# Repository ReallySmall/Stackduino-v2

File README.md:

Stackduino 2
==========
Please visit the project site for details: https://www.stackduino.net/boards/v2-2

Copyright 2017 Richard Iles

Permission is hereby granted, free of charge, to any person obtaining a copy of this software and associated documentation files (the "Software"), to deal in the Software without restriction, including without limitation the rights to use, copy, modify, merge, publish, distribute, sublicense, and/or sell copies of the Software, and to permit persons to whom the Software is furnished to do so, subject to the following conditions:

The above copyright notice and this permission notice shall be included in all copies or substantial portions of the Software.

THE SOFTWARE IS PROVIDED "AS IS", WITHOUT WARRANTY OF ANY KIND, EXPRESS OR IMPLIED, INCLUDING BUT NOT LIMITED TO THE WARRANTIES OF MERCHANTABILITY, FITNESS FOR A PARTICULAR PURPOSE AND NONINFRINGEMENT. IN NO EVENT SHALL THE AUTHORS OR COPYRIGHT HOLDERS BE LIABLE FOR ANY CLAIM, DAMAGES OR OTHER LIABILITY, WHETHER IN AN ACTION OF CONTRACT, TORT OR OTHERWISE, ARISING FROM, OUT OF OR IN CONNECTION WITH THE SOFTWARE OR THE USE OR OTHER DEALINGS IN THE SOFTWARE.

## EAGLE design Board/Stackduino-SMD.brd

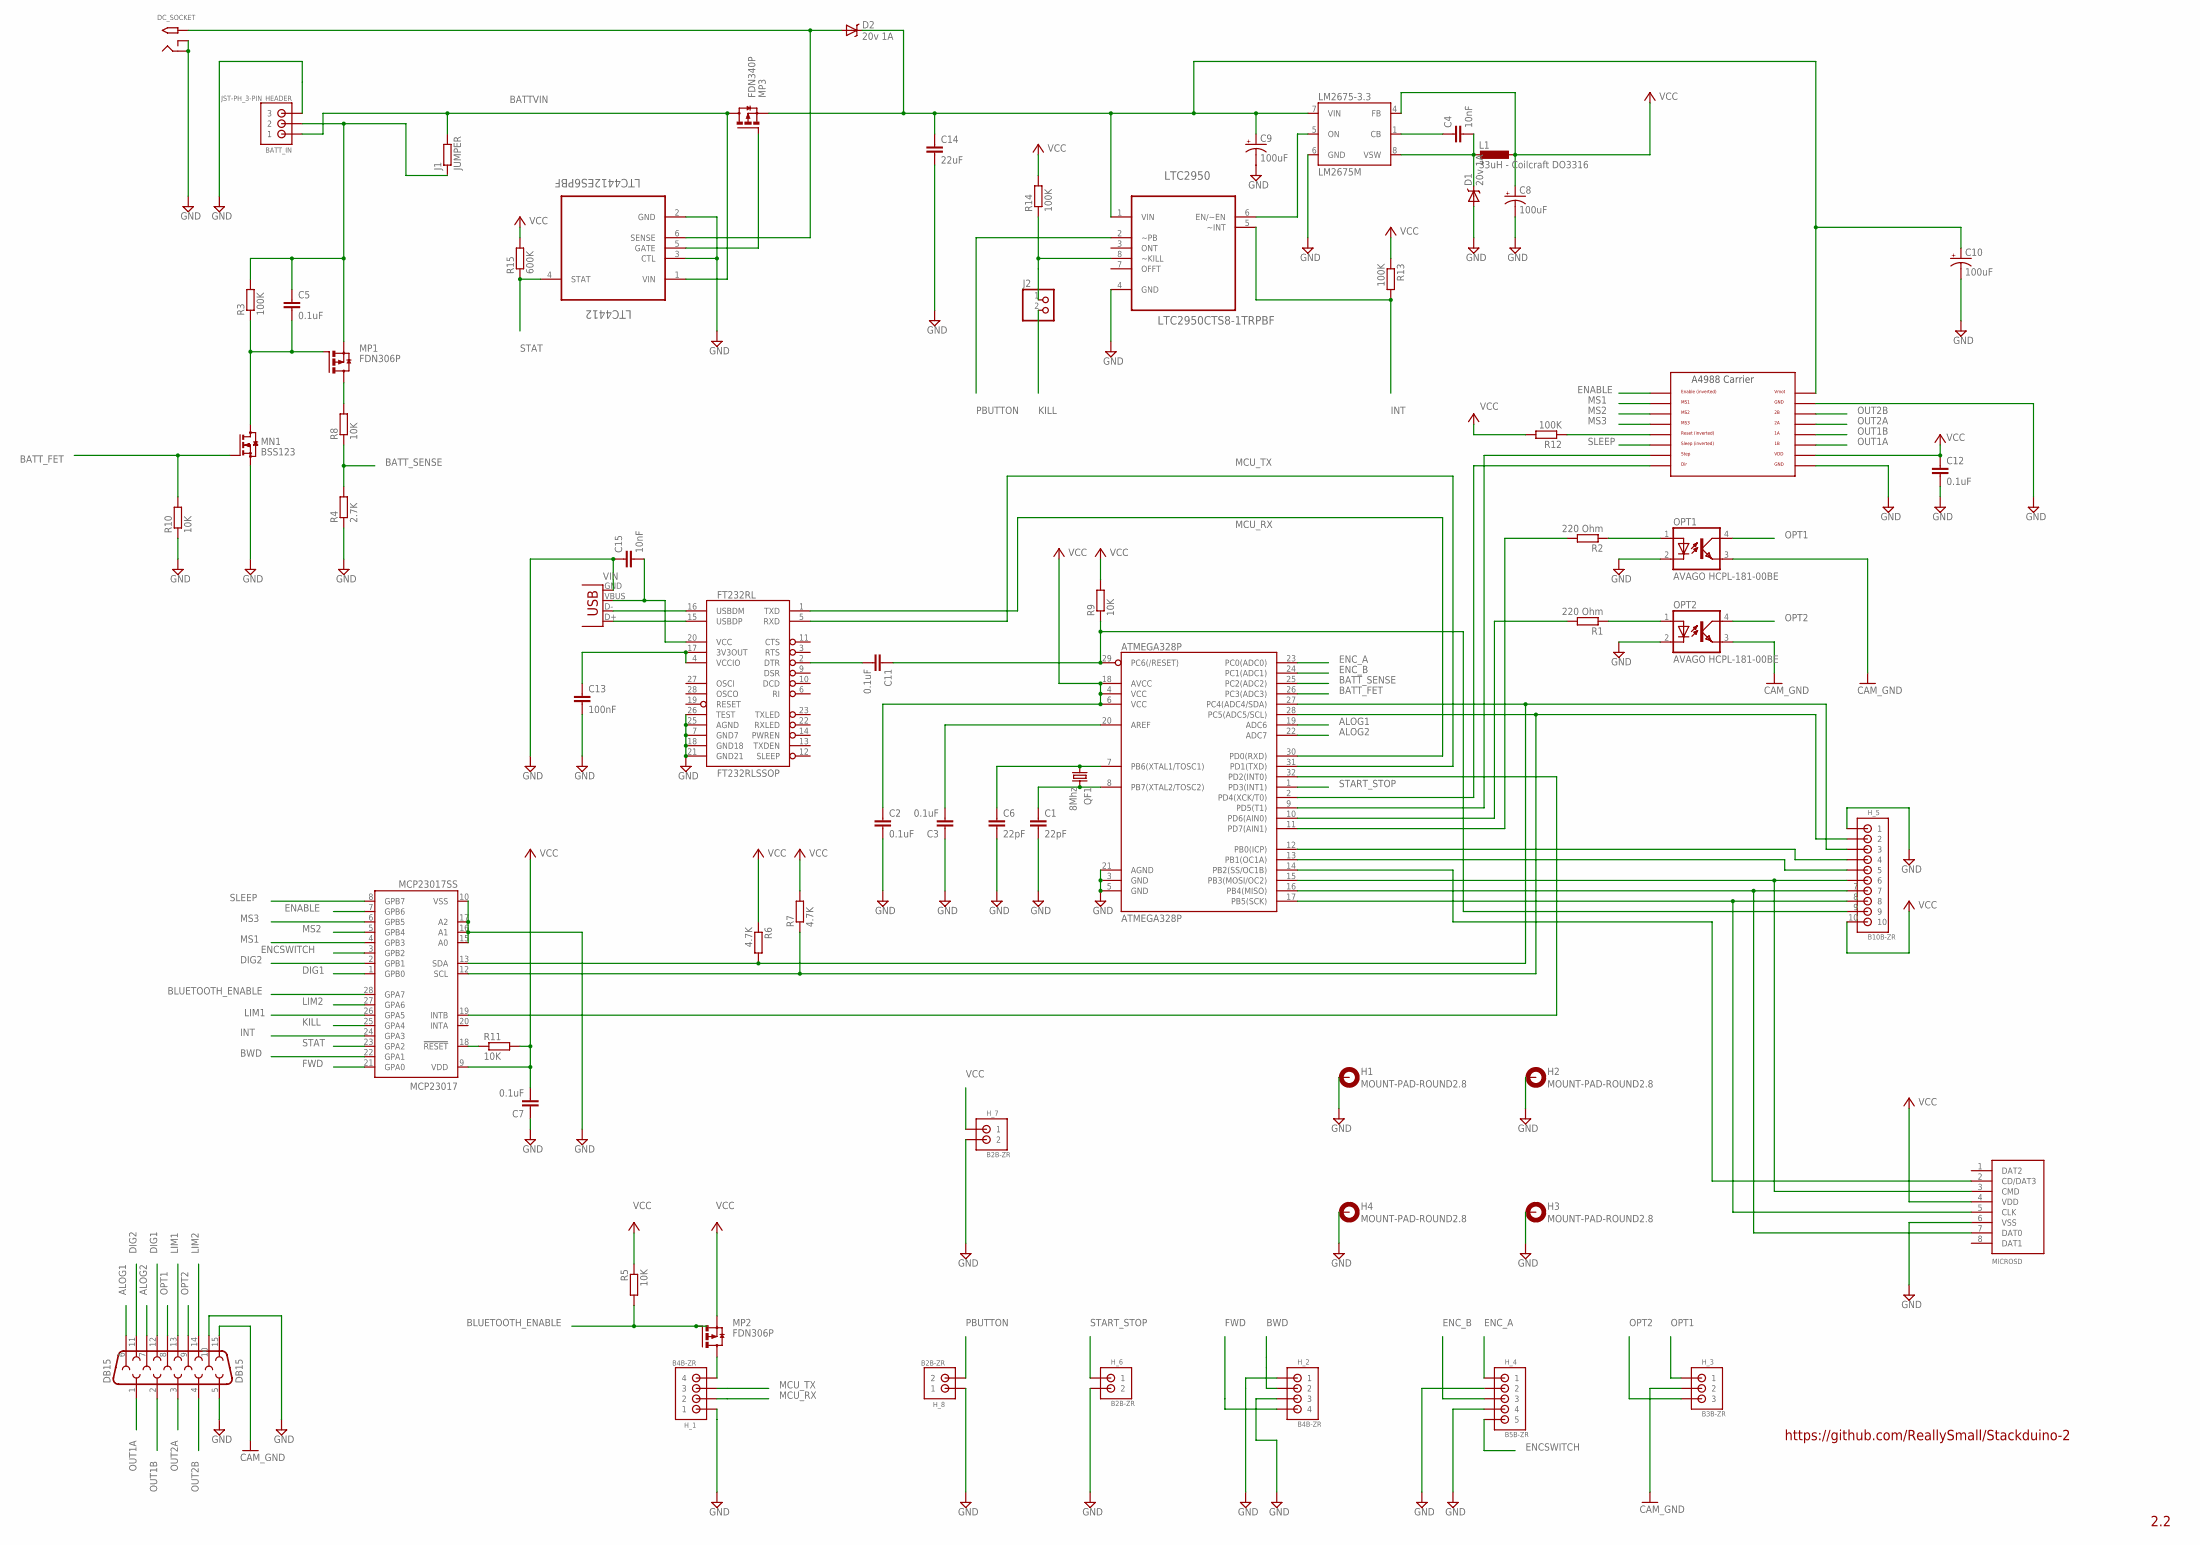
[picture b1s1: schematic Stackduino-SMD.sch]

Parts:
A4988_CARRIER: A4988BREAKOUT
ATMEGA328P: ATMEGA328P; TQFP32-08
BATT_IN: JST-PH_3-PIN_HEADER; JST_B3B-PH_HEADER
C1, C6: 22pF; C0805
C2, C3, C5, C7, C11, C12: 0.1uF; C0805
C4, C15: 10nF; C0805
C8, C9, C10: 100uF; PANASONIC_D
C13: 100nF; C0805
C14: 22uF; C0805
D1, D2: 20v 1A; SMA-DIODE
DB15: DB15
DC_SOCKET: 2.1MMJACKTHM; PJ-102A
FT232RL: FT232RLSSOP; SSOP28DB
H1, H2, H3, H4: MOUNT-PAD-ROUND2.8; 2,8-PAD
H_1, H_2: B4B-ZR
H_3: B3B-ZR
H_4: B5B-ZR
H_5: B10B-ZR
H_6, H_7, H_8: B2B-ZR
J1: JUMPER; R0805
J2: PINHD-1X2; 1X02
L1: 33uH - Coilcraft DO3316; DO3316P
LM2675-3.3: LM2675M; SO08
LTC2950: LTC2950CTS8-1TRPBF; SOT65P280X100-8N
LTC4412: LTC4412ES6PBF; SOT95P280X100-6N
MCP23017: MCP23017SS; SSOP28
MICROSD: CON_MICROSDHINGED; CON_MICROSD_HINGED
MN1: BSS123; SOT23
MP1, MP2: FDN306P; SUPER-SOT3
MP3: FDN340P; SUPER-SOT3
OPT1, OPT2: AVAGO HCPL-181-00BE; SMD4
QF1: 8Mhz; HC49U-V
R1, R2: 220 Ohm; R0805
R3, R12, R13, R14: 100K; R0805
R4: 2.7K; R0805
R5, R8, R9, R10, R11: 10K; R0805
R6, R7: 4.7K; R0805
R15: 600K; R0805
USB: USBSMD; USB-MINIB

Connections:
3V3_SET: C13.1, FT232RL.4 (VCCIO), FT232RL.17 (3V3OUT)
A4988_RESET: A4988_CARRIER.RST, R12.1
ALOG1: ATMEGA328P.19 (ADC6), DB15.6
ALOG2: ATMEGA328P.22 (ADC7), DB15.7
BATTVIN: BATT_IN.P1 (1), J1.2, LTC4412.1 (VIN), MP3.3 (D)
BATT_FET: ATMEGA328P.26 (PC3(ADC3)), MN1.1 (G), R10.2
BATT_SENSE: ATMEGA328P.25 (PC2(ADC2)), R4.2, R8.1
BATT_SENSE_UPSTREAM: MP1.3 (D), R8.2
BATT_VOLT: BATT_IN.P2 (2), C5.1, J1.1, MP1.2 (S), R3.2
BATT_VOLT_ENABLE: C5.2, MN1.3 (D), MP1.1 (G), R3.1
BLUETOOTH_ENABLE: MCP23017.28 (GPA7), MP2.1 (G), R5.2
BWD: H_2.2, MCP23017.22 (GPA1)
CAM_GND: DB15.15, H_3.2, OPT1.3 (EMIT), OPT2.3 (EMIT)
DIG1: DB15.12, MCP23017.1 (GPB0)
DIG2: DB15.11, MCP23017.2 (GPB1)
DIR: A4988_CARRIER.DIR, ATMEGA328P.2 (PD4(XCK/T0))
ENABLE: A4988_CARRIER.EN, MCP23017.7 (GPB6)
ENCSWITCH: H_4.5, MCP23017.3 (GPB2)
ENC_A: ATMEGA328P.23 (PC0(ADC0)), H_4.1
ENC_B: ATMEGA328P.24 (PC1(ADC1)), H_4.3
FWD: H_2.4, MCP23017.21 (GPA0)
GATE: LTC4412.5 (GATE), MP3.1 (G)
GND: A4988_CARRIER.GND, A4988_CARRIER.GND@0 (GND), ATMEGA328P.3 (GND), ATMEGA328P.5 (GND), ATMEGA328P.21 (AGND), BATT_IN.P3 (3), C1.2, C2.2, C3.1, C6.2, C7.1, C8.-, C9.-, C10.-, C12.2, C13.2, C14.2, C15.1, D1.A, DB15.5, DB15.10, DC_SOCKET.RING, DC_SOCKET.RING_SW, FT232RL.7 (GND7), FT232RL.18 (GND18), FT232RL.21 (GND21), FT232RL.25 (AGND), FT232RL.26 (TEST), H1.B2,8, H2.B2,8, H3.B2,8, H4.B2,8, H_1.1, H_2.1, H_2.3, H_4.2, H_4.4, H_5.1, H_6.2, H_7.2, H_8.1, LM2675-3.3.6 (GND), LTC2950.4 (GND), LTC4412.2 (GND), LTC4412.3 (CTL), MCP23017.10 (VSS), MCP23017.15 (A0), MCP23017.16 (A1), MCP23017.17 (A2), MICROSD.6 (VSS), MN1.2 (S), OPT1.2 (C), OPT2.2 (C), R4.1, R10.1, USB.GND
I2C_SCL: ATMEGA328P.28 (PC5(ADC5/SCL)), H_5.2, MCP23017.12 (SCL), R7.1
I2C_SDA: ATMEGA328P.27 (PC4(ADC4/SDA)), H_5.3, MCP23017.13 (SDA), R6.2
INT: LTC2950.5 (~INT), MCP23017.24 (GPA3), R13.2
KILL: J2.2, MCP23017.25 (GPA4)
KILL_2: J2.1, LTC2950.8 (~KILL), R14.1
LIM1: DB15.13, MCP23017.26 (GPA5)
LIM2: DB15.14, MCP23017.27 (GPA6)
LM2675_CB: C4.1, LM2675-3.3.1 (CB)
LM2675_ENABLE: LM2675-3.3.5 (ON), LTC2950.6 (EN/~EN)
LM2675_OUT: C4.2, D1.C, L1.1, LM2675-3.3.8 (VSW)
MCP_INT: ATMEGA328P.32 (PD2(INT0)), MCP23017.19 (INTB)
MCP_RESET: MCP23017.18 (!RESET), R11.1
MCU_RX: ATMEGA328P.30 (PD0(RXD)), FT232RL.1 (TXD), H_1.2
MCU_TX: ATMEGA328P.31 (PD1(TXD)), FT232RL.5 (RXD), H_1.3
MISO: ATMEGA328P.16 (PB4(MISO)), H_5.7, MICROSD.7 (DAT0)
MOSI: ATMEGA328P.15 (PB3(MOSI/OC2)), H_5.6, MICROSD.3 (CMD)
MS1: A4988_CARRIER.MS1, MCP23017.4 (GPB3)
MS2: A4988_CARRIER.MS2, MCP23017.5 (GPB4)
MS3: A4988_CARRIER.MS3, MCP23017.6 (GPB5)
unnamed: C11.2, FT232RL.2 (DTR)
unnamed: FT232RL.16 (USBDM), USB.D-
unnamed: FT232RL.15 (USBDP), USB.D+
unnamed: ATMEGA328P.20 (AREF), C3.2
unnamed: H_1.4, MP2.3 (D)
unnamed: C15.2, FT232RL.20 (VCC), USB.VBUS
OPT1: DB15.8, H_3.1, OPT1.4 (COL)
OPT1_IN: OPT1.1 (A), R2.1
OPT1_MCU: ATMEGA328P.11 (PD7(AIN1)), R2.2
OPT2: DB15.9, H_3.3, OPT2.4 (COL)
OPT2_IN: OPT2.1 (A), R1.1
OPT2_MCU: ATMEGA328P.10 (PD6(AIN0)), R1.2
OUT1A: A4988_CARRIER.1B, DB15.1
OUT1B: A4988_CARRIER.1A, DB15.2
OUT2A: A4988_CARRIER.2A, DB15.3
OUT2B: A4988_CARRIER.2B, DB15.4
PBUTTON: H_8.2, LTC2950.2 (~PB)
RESET: ATMEGA328P.29 (PC6(/RESET)), C11.1, H_5.9, R9.1
SCK: ATMEGA328P.17 (PB5(SCK)), H_5.8, MICROSD.5 (CLK)
SLEEP: A4988_CARRIER.SLP (SLEEP), MCP23017.8 (GPB7)
SS_1: ATMEGA328P.14 (PB2(SS/OC1B)), MICROSD.2 (CD/DAT3)
SS_2: ATMEGA328P.13 (PB1(OC1A)), H_5.5
SS_3: ATMEGA328P.12 (PB0(ICP)), H_5.4
START_STOP: ATMEGA328P.1 (PD3(INT1)), H_6.1
STAT: LTC4412.4 (STAT), MCP23017.23 (GPA2), R15.1
STEP: A4988_CARRIER.STEP, ATMEGA328P.9 (PD5(T1))
V+: A4988_CARRIER.VMOT, C9.+, C10.+, C14.1, D2.C, LM2675-3.3.7 (VIN), LTC2950.1 (VIN), MP3.2 (S)
VCC: A4988_CARRIER.VDD, ATMEGA328P.4 (VCC), ATMEGA328P.6 (VCC), ATMEGA328P.18 (AVCC), C2.1, C7.2, C8.+, C12.1, H_5.10, H_7.1, L1.2, LM2675-3.3.4 (FB), MCP23017.9 (VDD), MICROSD.4 (VDD), MP2.2 (S), R5.1, R6.1, R7.2, R9.2, R11.2, R12.2, R13.1, R14.2, R15.2
VIN: D2.A, DC_SOCKET.TIP, LTC4412.6 (SENSE)
XTAL1: ATMEGA328P.7 (PB6(XTAL1/TOSC1)), C6.1, QF1.1
XTAL2: ATMEGA328P.8 (PB7(XTAL2/TOSC2)), C1.1, QF1.2

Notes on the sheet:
https://github.com/ReallySmall/Stackduino-2
2.2

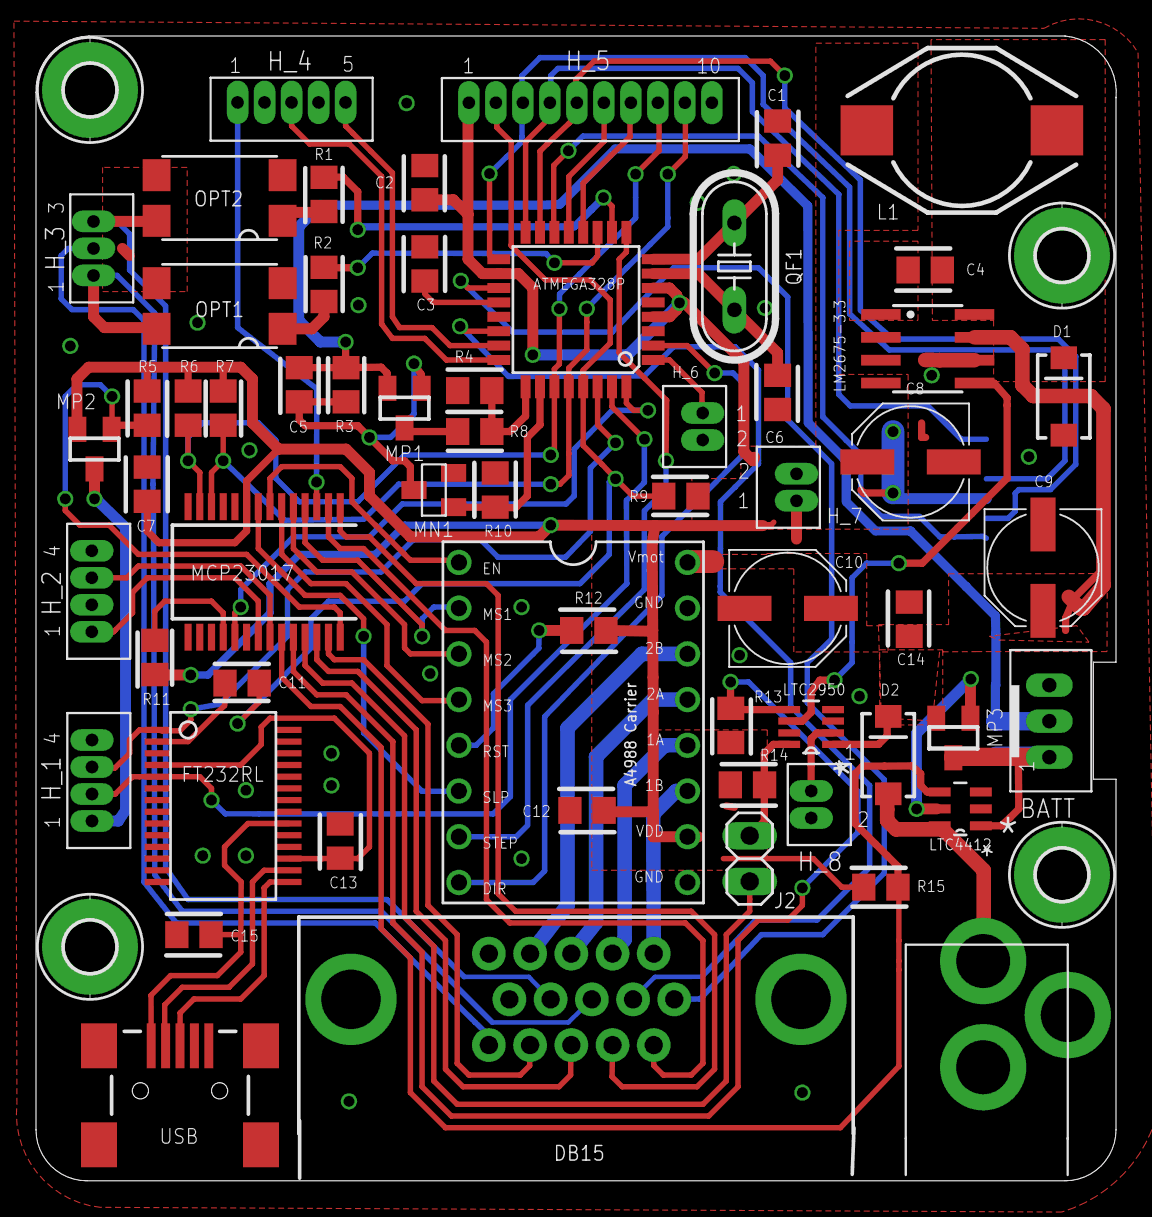
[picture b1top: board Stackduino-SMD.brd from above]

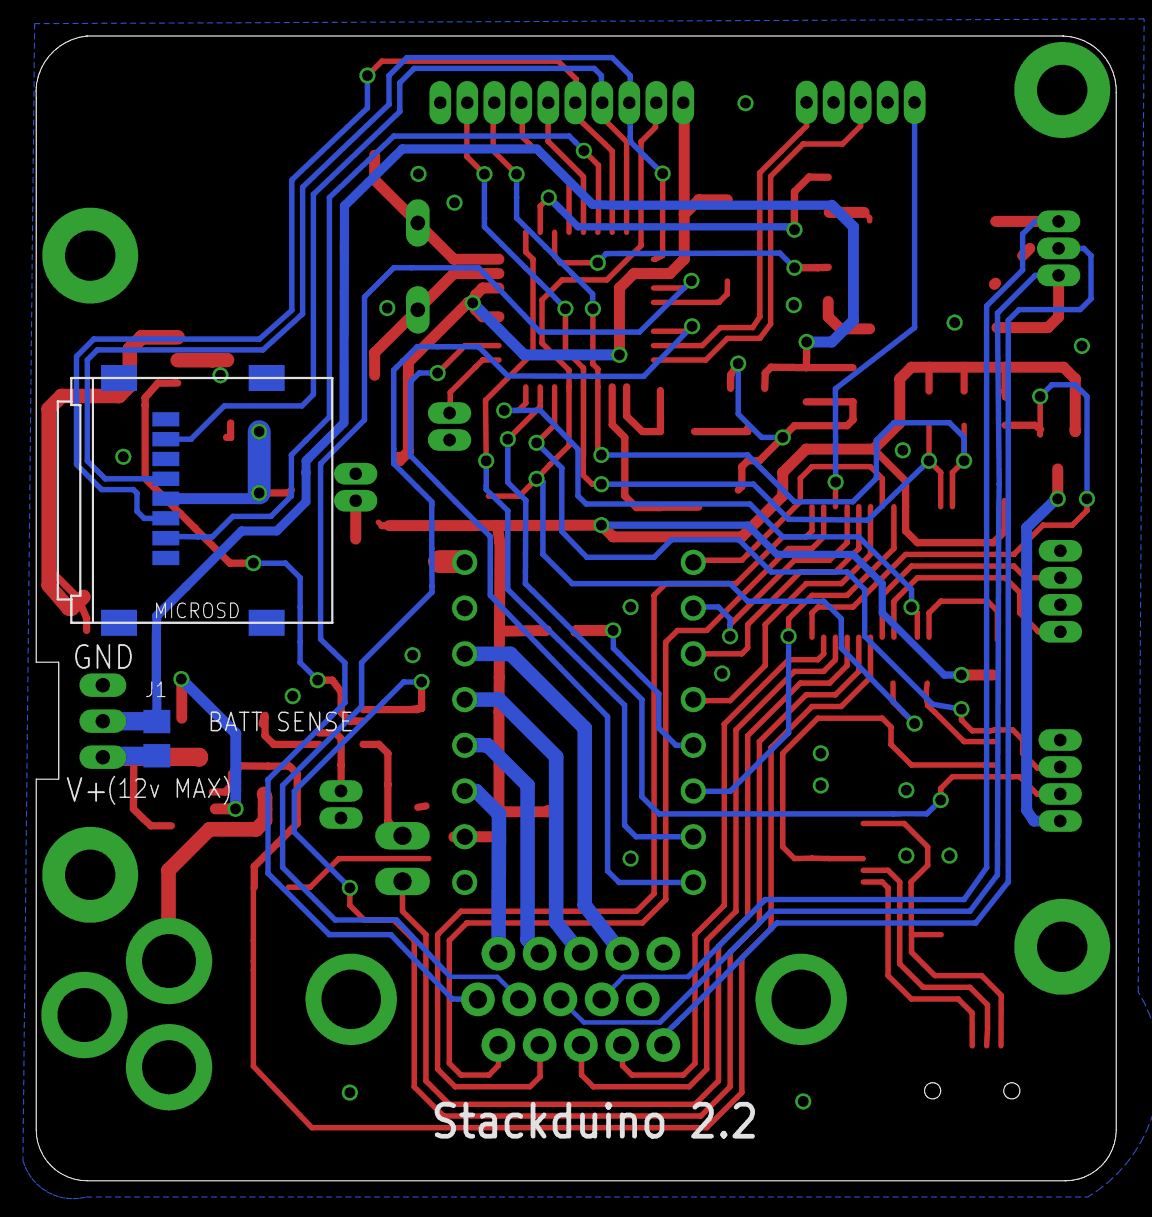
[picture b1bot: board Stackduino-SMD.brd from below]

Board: 2 copper layers, 60.0 x 63.6 mm, 66 parts (2 on the bottom side), 73 nets.

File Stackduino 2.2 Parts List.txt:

Partlist

Exported from Stackduino-SMD.sch at 26/02/2015 19:54:02

EAGLE Version 7.2.0 Copyright (c) 1988-2014 CadSoft

Assembly variant: 

Part          Value                   Device              Package            Library                  Sheet

A4988_CARRIER A4988BREAKOUT           A4988BREAKOUT       A4988BREAKOUT      RepRapjr                 1
ATMEGA328P    ATMEGA328P              ATMEGA328_SMT       TQFP32-08          SparkFun-DigitalIC       1
BATT_IN       JST-PH_3-PIN_HEADER     JST-PH_3-PIN_HEADER JST_B3B-PH_HEADER  SRG                      1
C1            22pF                    C                   C0805              eagle-ltspice            1
C2            0.1uF                   C                   C0805              eagle-ltspice            1
C3            0.1uF                   C                   C0805              eagle-ltspice            1
C4            10nF                    C                   C0805              eagle-ltspice            1
C5            0.1uF                   C                   C0805              eagle-ltspice            1
C6            22pF                    C                   C0805              eagle-ltspice            1
C7            0.1uF                   C                   C0805              eagle-ltspice            1
C8            100uF                   CAP_POLD            PANASONIC_D        SparkFun-Passives        1
C9            100uF                   CAP_POLD            PANASONIC_D        SparkFun-Passives        1
C10           100uF                   CAP_POLD            PANASONIC_D        SparkFun-Passives        1
C11           0.1uF                   C                   C0805              eagle-ltspice            1
C12           0.1uF                   C                   C0805              eagle-ltspice            1
C13           100nF                   C                   C0805              eagle-ltspice            1
C14           22uF                    C                   C0805              eagle-ltspice            1
C15           10nF                    C                   C0805              eagle-ltspice            1
D1            20v 1A                  MBRA140             SMA-DIODE          SparkFun-DiscreteSemi    1
D2            20v 1A                  MBRA140             SMA-DIODE          SparkFun-DiscreteSemi    1
DB15          DB15                    DB15                DB15               SparkFun-Connectors      1
DC_SOCKET     2.1MMJACKTHM            2.1MMJACKTHM        PJ-102A            adafruit                 1
FT232RL       FT232RLSSOP             FT232RLSSOP         SSOP28DB           SparkFun-DigitalIC       1
H1            MOUNT-PAD-ROUND2.8      MOUNT-PAD-ROUND2.8  2,8-PAD            holes                    1
H2            MOUNT-PAD-ROUND2.8      MOUNT-PAD-ROUND2.8  2,8-PAD            holes                    1
H3            MOUNT-PAD-ROUND2.8      MOUNT-PAD-ROUND2.8  2,8-PAD            holes                    1
H4            MOUNT-PAD-ROUND2.8      MOUNT-PAD-ROUND2.8  2,8-PAD            holes                    1
H_1           B4B-ZR                  B4B-ZR              B4B-ZR             jst-connectors           1
H_2           B4B-ZR                  B4B-ZR              B4B-ZR             jst-connectors           1
H_3           B3B-ZR                  B3B-ZR              B3B-ZR             jst-connectors           1
H_4           B5B-ZR                  B5B-ZR              B5B-ZR             jst-connectors           1
H_5           B10B-ZR                 B10B-ZR             B10B-ZR            jst-connectors           1
H_6           B2B-ZR                  B2B-ZR              B2B-ZR             jst-connectors           1
H_7           B2B-ZR                  B2B-ZR              B2B-ZR             jst-connectors           1
H_8           B2B-ZR                  B2B-ZR              B2B-ZR             jst-connectors           1
J1            JUMPER                  R                   R0805              eagle-ltspice            1
J2                                    PINHD-1X2           1X02               pinhead                  1
L1            33uH - Coilcraft DO3316 DO3316P             DO3316P            inductor-coilcraft       1
LM2675-3.3    LM2675M                 LM2675M             SO08               v-reg-3                  1
LTC2950       LTC2950CTS8-1TRPBF      LTC2950CTS8-1TRPBF  SOT65P280X100-8N   LTC_By_element14_Batch_1 1
LTC4412       LTC4412ES6PBF           LTC4412ES6PBF       SOT95P280X100-6N   LTC_By_element14_Batch_1 1
MCP23017      MCP23017SS              MCP23017SS          SSOP28             adafruit                 1
MICROSD       CON_MICROSDHINGED       CON_MICROSDHINGED   CON_MICROSD_HINGED dp_devices               1
MN1           BSS123                  BSS123              SOT23              transistor-small-signal  1
MP1           FDN306P                 FDN360P             SUPER-SOT3         transistor-power         1
MP2           FDN306P                 FDN360P             SUPER-SOT3         transistor-power         1
MP3           FDN340P                 FDN360P             SUPER-SOT3         transistor-power         1
OPT1          AVAGO HCPL-181-00BE     LTV816S             SMD4               optocoupler              1
OPT2          AVAGO HCPL-181-00BE     LTV816S             SMD4               optocoupler              1
QF1           8Mhz                    CRYSTALHC49U-V      HC49U-V            crystal                  1
R1            220 Ohm                 R                   R0805              eagle-ltspice            1
R2            220 Ohm                 R                   R0805              eagle-ltspice            1
R3            100K                    R                   R0805              eagle-ltspice            1
R4            2.7K                    R                   R0805              eagle-ltspice            1
R5            10K                     R                   R0805              eagle-ltspice            1
R6            4.7K                    R                   R0805              eagle-ltspice            1
R7            4.7K                    R                   R0805              eagle-ltspice            1
R8            10K                     R                   R0805              eagle-ltspice            1
R9            10K                     R                   R0805              eagle-ltspice            1
R10           10K                     R                   R0805              eagle-ltspice            1
R11           10K                     R                   R0805              eagle-ltspice            1
R12           100K                    R                   R0805              eagle-ltspice            1
R13           100K                    R                   R0805              eagle-ltspice            1
R14           100K                    R                   R0805              eagle-ltspice            1
R15           100K                    R                   R0805              eagle-ltspice            1
USB           USBSMD                  USBSMD              USB-MINIB          SparkFun-Connectors      1

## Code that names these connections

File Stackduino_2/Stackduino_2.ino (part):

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#define _Digole_Serial_I2C_ // OLED screen configured with solder jumper to run in I2C mode
#define OLED_ROWS 4 // OLED text rows
#define OLED_COLS 16 // OLED text columns
#define ENC_A A0 // Rotary encoder
#define ENC_B A1 // Rotary encoder
#define ENC_PORT PINC // Rotary encoder
#define settings_elements 4 // Number of properties in each settings

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

/* SET UP REMAINING ATMEGA PINS */
const byte mcp_int = 2; // Incoming MCP23017 interrupts
const byte btn_main = 3;  // Main start/ stop stack button
const byte step_dir = 4; // Direction pin on A4988 stepper driver
const byte do_step = 5; // Step pin on A4988 stepper driver
const byte cam_focus = 6; // Camera autofocus signal
const byte cam_shutter = 7; // Camera shutter signal
const byte sd_ss = 10; // SPI slave select for SD card slot
const byte batt_sense = A2; // Battery voltage sampling
const byte batt_fet = 17; // Connect/ disconnect battery voltage sampling line
const byte alog_1 = A6; // Analogue pin (supports analogueRead() only) broken out through DB15 - currently unused
const byte alog_2 = A7; // Analogue pin (supports analogueRead() only) broken out through DB15 - currently unused

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/*  SET UP MCP23017 PINS */
const byte step_bwd = 0; // For manual stage positioning
const byte step_fwd = 1; // For manual stage positioning
const byte pwr_stat = 2; // LTC4412 stat pin - indicates whether controller is currently powered by wall adapter or battery
const byte switch_off_flag = 3; // LTC2950 int pin - signals to the controller that it is about to be switched off
const byte switch_off = 4; // LTC2950 kill pin - disables 3.3v regulator and switches off controller
const byte limit_switch_front = 5; // Limit switch to stop stepper motor if end of travel is reached
const byte limit_switch_back = 6; // Limit switch to stop stepper motor if end of travel is reached
const byte bluetooth_pwr_toggle = 7; // Toggles power to bluetooth breakout board header
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void setup() {

  /* SET ATMEGA PINMODES AND PULLUPS */
  pinMode(mcp_int, INPUT); digitalWrite(mcp_int, HIGH);
  pinMode(btn_main, INPUT); digitalWrite(btn_main, HIGH);
  pinMode(ENC_A, INPUT); digitalWrite(ENC_A, HIGH);
  pinMode(ENC_B, INPUT); digitalWrite(ENC_B, HIGH);
  pinMode(step_dir, OUTPUT); digitalWrite(step_dir, LOW);
  pinMode(do_step, OUTPUT); digitalWrite(do_step, LOW);
  pinMode(cam_focus, OUTPUT); digitalWrite(cam_focus, LOW);
  pinMode(cam_shutter, OUTPUT); digitalWrite(cam_shutter, LOW);
  pinMode(batt_fet, OUTPUT); digitalWrite(batt_fet, LOW);
  pinMode(sd_ss, OUTPUT);

  /* START MCP23017 AND SET PINMODES AND PULLUPS */
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  attachInterrupt(0, mcpInterrupt, FALLING); // ATMega external interrupt 0
  attachInterrupt(1, cancelStack, FALLING); // ATMega external interrupt 1

  pciSetup(ENC_A); // ATMega pin change interrupt
  pciSetup(ENC_B); // ATMega pin change interrupt

  mcp.setupInterrupts(true, false, LOW); // MCP23017 interupts (trigger ATMega external interrupt 0)
  mcp.setupInterruptPin(switch_off_flag, FALLING);
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
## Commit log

2013-12-07 FT232RL circuit added
2013-12-08 Various additions
2013-12-08 Completed draft breadboard layout
2014-01-05 nitial commit of stackduino eagle library
2014-01-19 Initial commit of eagle files
2014-01-20 Latest progress on schematic
2014-01-22 Added a3967 wiring
2014-01-24 Latest progress
2014-01-31 Initial layout of board
2014-02-17 Substituted in a4988 polulu driver
2014-03-30 Fixed tx/rx and test pin errors
2014-03-31 Copied in Stackduino 1 sketch to adapt
2014-04-05 Added preliminary sketch and required libs
2014-04-06 Progress on sketch
2014-04-08 added further mcp interrupt functions
2014-04-12 Amended cap values on crystal
2014-04-12 added power source sensing on startup
2014-04-13 More screen additions
2014-04-14 Added countdown on camera pause
2014-04-16 reconfigured encoder listening
2014-04-17 Added readme
2014-04-17 Create gh-pages branch via GitHub
2014-04-17 fixed hang on interrupt
2014-04-24 Added dc adapter symbol
2014-05-28 changes inc battery monitor
2014-06-01 Battery monitor and VMOT Mosfets added
2014-06-04 reorganised traces to avoid inductor
2014-06-05 Changed inductor placement
2014-06-06 added camera input
2014-06-08 Beginning to re-layout traces on grid
2014-06-18 latest progress on brd v2.1
2014-06-29 topside board nearly complete
2014-07-12 nearly there,,,
2014-07-17 no errors in DRC!
2014-07-20 Ready for checking
2014-07-21 Cleared ERC warnings
2014-07-26 Cleaned up code
2014-08-02 switching to 3.3v, reworked mosfets
2014-08-08 silkscreen outlines to 0805 caps and resistors
2014-08-30 Slight change to jst footprint plus solder stencil
2014-09-19 initial code for battery monitoring and bluetooth
2014-09-19 added pinouts and component list
2014-10-09 debugging in progress
2014-10-17 Battery monitor working and calibrated
2014-10-25 Trying to get mcp23017 interrupts working
2014-10-26 debugging manual_control_forward
2014-11-02 fwd manual control fixed and non-blocking delays
2014-11-04 Sketch refactoring
2014-11-04 refactoring
2014-11-05 auto centre menu items
2014-11-20 Tinkering with pin change interrupts
2014-11-21 building in support for control over serial
2014-11-23 rotary encoder interrupts testing
2014-11-25 added cronJob functions
2014-11-25 removed orphaned variable
2014-11-26 various testing
2014-11-27 misc tinkering
2014-11-30 adding comments
2014-11-30 refactoring menus
2014-12-04 Refactoring menus with char arrays
2014-12-05 Replaced uses of String with char arrays
2014-12-06 added application connection status
2014-12-07 adding icons for application connection
2015-02-07 Added json library and removed sleep mode
2015-02-25 added sd card read/ write functions
    plus refactor to reduce memory size
2015-02-26 Updated parts list for v2.2
    and removed out of date infor for v2.1
    Please enter the commit message for your changes. Lines starting
2015-03-07 added sketchup model for enclosure planning
2015-04-19 Fixed load settings from SD
2015-04-20 load settings
2015-04-21 Real time progress bar
2015-04-23 char instead of ints for menu variables
2015-04-24 added flash strings for system messages
2015-05-01 Fixed load function error
2015-05-03 Automatic centred printing
2015-05-04 Save settings to temp file
2015-05-07 manual control
2015-05-08 short and long press manual control
2015-05-10 test images
2015-05-10 reverted to old pause countdown method
2015-05-11 cancel stack
2015-05-12 commit before testing new struct
2015-05-13 record time elapsed for stack
2015-05-15 fixed pwr_stat interrupt
2015-05-17 take individual images
2015-05-25 consolidated button debouncing
2015-06-13 fixed incorrect reistor value
2015-09-26 File tidyup
2017-01-08 Folder tidyup
2017-02-14 Added Eagle files for board

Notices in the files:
parts and their libraries:
SparkFun-DigitalIC: Licensing: CC v3.0 Share-Alike You are welcome to use this library for commercial purposes.
